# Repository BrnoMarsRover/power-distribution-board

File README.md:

# Power distribution board

Everything for the BrnoMarsRover power distribution board: the schematic and PCB, the
firmware that runs on it, and the ROS 2 driver that consumes it.

```
kicad/      schematic and PCB
pdf/        exported schematics
firmware/   Raspberry Pi Pico 2 sketch (Arduino, arduino-pico core)
ros2/       ROS 2 driver package (ament_python, Humble)
```

The firmware and the driver live together **because they share a versioned wire
protocol**. Every field name and status bit below is written twice - once in
`firmware/PowerBoard/Functions.cpp` and once in `ros2/powerboard/powerboard/powerboard_node.py`.
Splitting them across repositories would let the two halves be changed, reviewed and
deployed independently, and the failure mode is not a build error - it is silently
misparsed telemetry. Change the protocol in one commit, and bump `jsonSchemaVersion`
(firmware `Config.cpp`) together with `SUPPORTED_SCHEMA` (node) when you do.

## Hardware

Five INA238 current/voltage monitors on I2C, one per branch, each with a high-side
switch:

| Designator | I2C  | Shunt  | Rail             | Limit   |
|-----------|------|--------|------------------|---------|
| U2        | 0x40 | 3 mOhm | battery feed, and the master gate for the rest | 15 A |
| U3        | 0x41 | 5 mOhm | 24 V             | 2.5 A   |
| U4        | 0x42 | 5 mOhm | 15 V             | 4 A     |
| U5        | 0x43 | 5 mOhm | 12 V             | 5 A     |
| U6        | 0x44 | 5 mOhm | 5 V              | 12 A    |

Limits come from the 60 W rating of each DC-DC converter.

**Over-current protection ships disabled** (`ocpEnabled = false`). Some high-side
drivers were tripped by inrush and are bridged, so the board cannot actually switch
those branches off. Limits are still evaluated and reported, so an overload is visible
in telemetry even though nothing acts on it. `OCP ON` enables tripping if the hardware
is ever repaired.

Two things the board cannot measure, by construction:

- **Charging current.** The charger is wired on the battery side of U2's shunt, so
  charge current never crosses it. The driver infers charging from rising open-circuit
  voltage instead.
- **Currents above ~8 A on the INA CURRENT register**, which saturates there. The
  shunt-derived value is used for protection and for the `i` field because it has the
  range; `ir` is kept alongside it only for cross-checking.

## Serial protocol (schema v1)

USB CDC-ACM, one JSON object per line, telemetry at 2 Hz. Anything not starting with
`{` is human-readable diagnostics (`STATUS`, `RAW`) and is ignored by machine readers.

`"t"` gives the line type: `tel`, `evt`, `ack`, `err`, `info`.

### `tel` - periodic telemetry

```json
{"t":"tel","v":1,"seq":123,"up":61500,"ocp":0,"mst":1,"b":[ ... ]}
```

| Key   | Meaning                                        |
|-------|------------------------------------------------|
| `v`   | schema version                                  |
| `seq` | frame counter; gaps mean frames were lost       |
| `up`  | milliseconds since board boot                   |
| `ocp` | 1 if over-current protection is enabled         |
| `mst` | 1 if the U2 master branch is on                 |
| `b`   | one object per branch                           |

Each branch object:

| Key   | Unit | Meaning                                                   |
|-------|------|-----------------------------------------------------------|
| `n`   |      | designator, `U2`..`U6`                                    |
| `a`   |      | I2C address                                               |
| `s`   |      | status bits, see below                                    |
| `lim` | mA   | configured current limit                                  |
| `vb`  | V    | bus voltage                                               |
| `vs`  | mV   | shunt voltage                                             |
| `i`   | mA   | current derived from the shunt - **this is the real one** |
| `ir`  | mA   | INA CURRENT register, saturates at ~8 A, cross-check only |
| `tc`  | degC | INA die temperature                                       |
| `tr`  |      | cumulative trip count                                     |

Status bits in `s`:

| Bit  | Name        |
|------|-------------|
| 0x01 | online      |
| 0x02 | enabled     |
| 0x04 | tripped     |
| 0x08 | manual off  |
| 0x10 | powered     |
| 0x20 | over limit  |

### `evt` - pushed immediately, not on the telemetry tick

```json
{"t":"evt","up":61500,"ev":"over_limit","n":"U5","i":5200.0,"lim":5000,"ocp":0}
```

`ev` is one of `over_limit`, `over_limit_clear`, `ocp_trip`, `ocp_recover`. These are
pushed as they happen because with OCP disabled an over-limit event is the only
actionable signal the board can give.

### `ack` / `err` / `info`

```json
{"t":"ack","cmd":"JSON","msg":"json output"}
{"t":"err","cmd":"OFF U9","msg":"unknown branch"}
{"t":"info","fw":"...","v":1,"rails":5,"ocp":0}
```

### Commands (host to board, one per line)

| Command        | Effect                                          |
|----------------|-------------------------------------------------|
| `ON <U>`       | switch a branch on                              |
| `OFF <U>`      | switch a branch off                             |
| `OCP [ON|OFF]` | query or set over-current protection            |
| `RAW`          | dump every INA238 register, human readable      |
| `STATUS`       | human readable summary                          |
| `JSON`         | machine-readable output (the default)           |
| `HUMAN`        | switch to the plain-text table                  |
| `ONCE`         | emit a single telemetry frame                   |

## Firmware

Arduino sketch in `firmware/PowerBoard`, target Raspberry Pi Pico 2 (`rpipico2`),
arduino-pico core 5.5.1. Open `PowerBoard.ino` and flash it.

## ROS 2 driver

`ros2/powerboard`, ament_python, tested on Humble. Depends only on `rclpy`,
`std_msgs`, `sensor_msgs`, `diagnostic_msgs` and `python3-serial` - no custom
interfaces.

```bash
ros2 launch powerboard powerboard.launch.py
```

| Topic                | Type                       |
|----------------------|----------------------------|
| `~/battery`          | `sensor_msgs/BatteryState` |
| `~/rails/voltages`   | `std_msgs/Float32MultiArray` |
| `~/rails/currents`   | `std_msgs/Float32MultiArray` |
| `~/rails/powers`     | `std_msgs/Float32MultiArray` |
| `~/events`           | `std_msgs/String`          |
| `~/command`          | `std_msgs/String` (subscription, forwards any board command) |
| `/diagnostics`       | `diagnostic_msgs/DiagnosticArray` |

The rail arrays carry names in `layout.dim[i].label`, index-aligned with `data[i]`.

State of charge is estimated from a LiPo open-circuit-voltage curve, load-compensated
and smoothed, and published in `BatteryState.percentage`. It is a rough guide, not a
fuel gauge: between about 3.8 and 3.9 V/cell the curve is nearly flat, and below
3.7 V/cell it falls away sharply. Defaults assume Freya's **10S, 14.5 Ah** pack; see
`cell_count`, `design_capacity_ah` and `pack_resistance_ohm`.

**Only one process may hold the serial port.** Two readers steal bytes from each other,
which looks exactly like a flaky board - sequence gaps and a halved frame rate.

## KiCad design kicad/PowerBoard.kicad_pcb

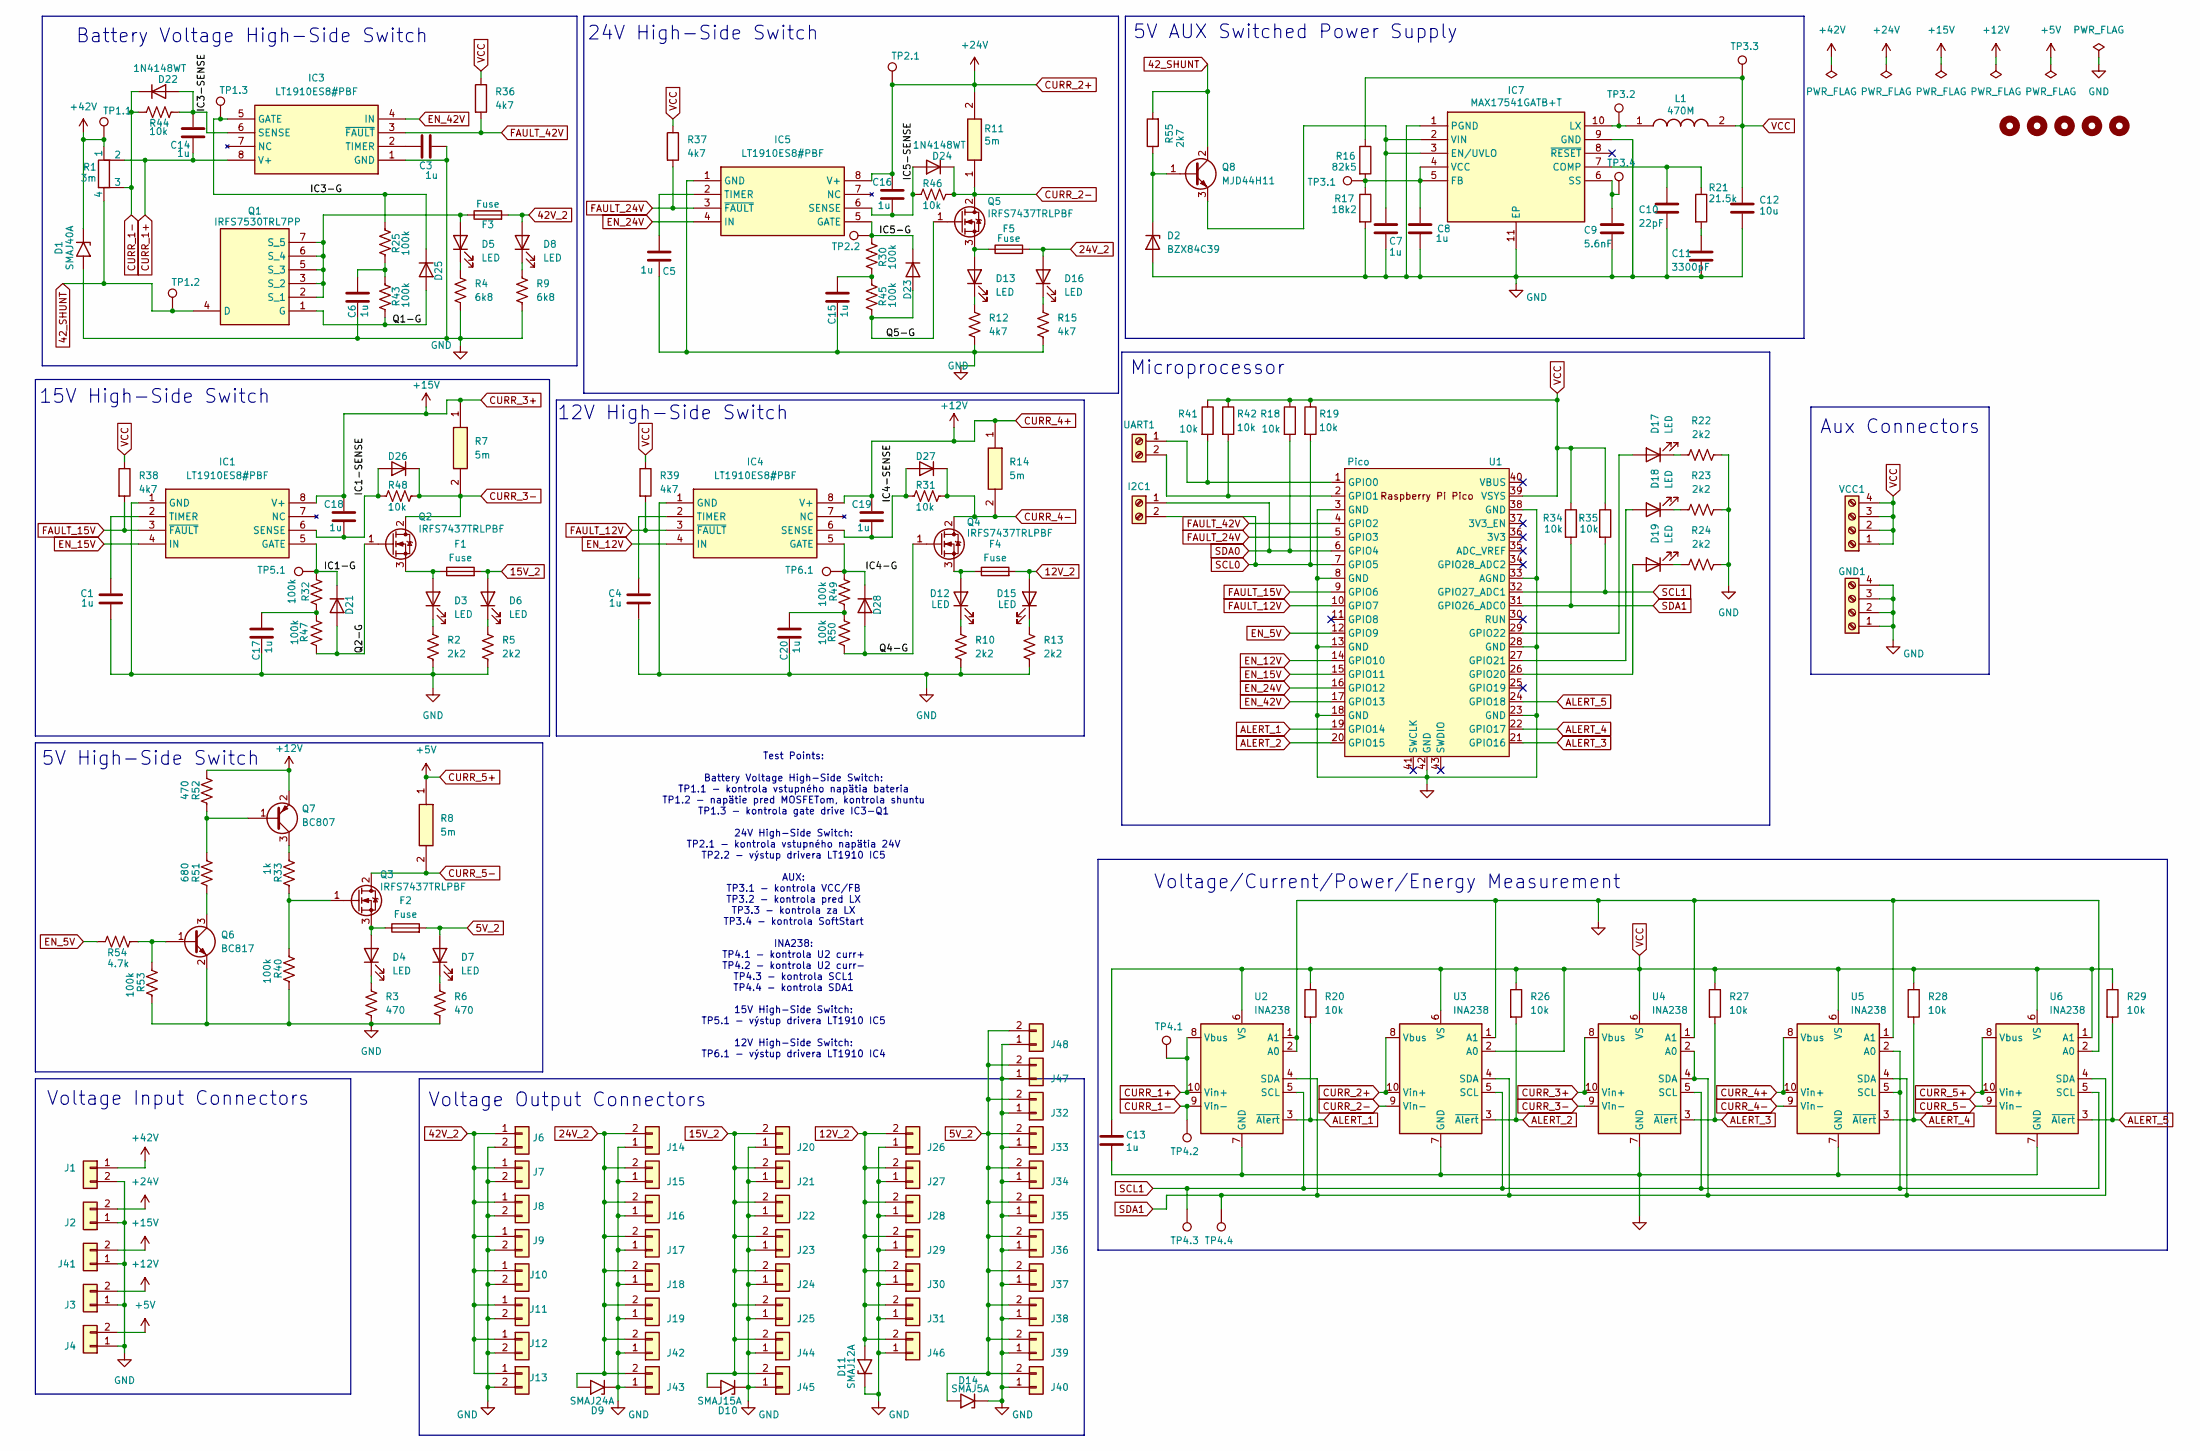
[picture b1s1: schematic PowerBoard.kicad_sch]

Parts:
C1, C3, C4, C5, C6, C7, C8, C14, C15, C16, C17, C18, C19, C20: 1u; C_0603_1608Metric
C9: 5.6nF; C_0603_1608Metric
C10: 22pF; C_0603_1608Metric
C11: 3300pF; C_0603_1608Metric
C12: 10u; C_0603_1608Metric
C13: 1u; C_1206_3216Metric
D1: SMAJ40A; D_SMA
D2: BZX84C39; SOT-23
D3, D4, D5, D6, D7, D8, D12, D13, D15, D16, D17, D18, D19: LED; D_1206_3216Metric
D9: SMAJ24A; D_SMA
D10: SMAJ15A; D_SMA
D11: SMAJ12A; D_SMA
D14: SMAJ5A; D_SMA
D21, D22, D23, D24, D25, D26, D27, D28: 1N4148WT; D_SOD-523
F1, F2, F3, F4, F5: Fuse; Fuse_Blade_ATO_directSolder
GND1: Screw_Terminal_01x04; TerminalBlock_Xinya_XY308-2.54-4P_1x04_P2.54mm_Horizontal
H1, H2, H3, H4, H5: MountingHole; MountingHole_3.2mm_M3
I2C1: Screw_Terminal_01x02; TerminalBlock_Xinya_XY308-2.54-2P_1x02_P2.54mm_Horizontal
IC1, IC3, IC4, IC5: LT1910ES8#PBF; SOIC127P599X175-8N; Mouser Part Number 584-LT1910ES8#PBF
IC7: MAX17541GATB+T; SON50P200X300X80-11N; Mouser Part Number 700-MAX17541GATB+T
J1, J6, J7, J8, J9, J10, J11, J12, J13: XT90
J2, J14, J15, J16, J17, J18, J19, J42, J43: DEAN_T; DEANS-T
J3, J20, J21, J22, J23, J24, J25, J26, J27, J28, J29, J30, J31, J41, J44, J45, J46: XT60; AMASS_XT60-F_1x02_P7.20mm_Vertical
J4, J32, J33, J34, J35, J36, J37, J38, J39, J40, J47, J48: XT30; AMASS_XT30U-F_1x02_P5.0mm_Vertical
L1: 470M; SRR5828A2R6Y; Mouser Part Number 6521-SRR5828A-470M
Q1: IRFS7530TRL7PP; Mouser Part Number 942-IRFS7530TRL7PP
Q2, Q3, Q4, Q5: IRFS7437TRLPBF; TO-263-2
Q6: BC817; SOT-23
Q7: BC807; SOT-23
Q8: MJD44H11; TO-252-2
R1: 3m; R_Shunt_Isabellenhuette_BVR4026
R2, R10: 2k2; R_0603_1608Metric
R3, R52: 470; R_0603_1608Metric
R4: 6k8; C_0603_1608Metric
R5, R13, R22, R23, R24: 2k2; R_1206_3216Metric
R6: 470; R_1206_3216Metric
R7, R8, R11, R14: 5m; RESC3216X89N; Mouser Part Number 71-WSL12061L000FEA
R9: 6k8; R_1206_3216Metric
R12: 4k7; R_0603_1608Metric
R15, R36, R37, R38, R39: 4k7; R_1206_3216Metric
R16: 82k5; R_0603_1608Metric
R17: 18k2; R_0603_1608Metric
R18, R19, R20, R26, R27, R28, R29, R34, R35, R41, R42: 10k; R_1206_3216Metric
R21: 21.5k; R_0603_1608Metric
R25, R30, R32, R40, R43, R45, R47, R49, R50, R53: 100k; R_0603_1608Metric
R31, R44, R46, R48: 10k; R_0603_1608Metric
R33: 1k; R_0603_1608Metric
R51: 680; R_0603_1608Metric
R54: 4.7k; R_0603_1608Metric
R55: 2k7; R_1206_3216Metric
TP1.1, TP1.2, TP1.3, TP2.1, TP2.2, TP3.1, TP3.2, TP3.3, TP3.4, TP4.1, TP4.2, TP4.3, TP4.4, TP5.1, TP6.1: TestPoint; TestPoint_Pad_1.0x1.0mm
U1: Pico; RPi_Pico_SMD_TH
U2, U3, U4, U5, U6: INA238; VSSOP-10_3x3mm_P0.5mm
UART1: Screw_Terminal_01x02; TerminalBlock_Xinya_XY308-2.54-2P_1x02_P2.54mm_Horizontal
VCC1: Screw_Terminal_01x04; TerminalBlock_Xinya_XY308-2.54-4P_1x04_P2.54mm_Horizontal

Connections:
5V_2: D7.2 (A), D14.2 (A2), F2.2, J32.2, J33.2, J34.2, J35.2, J36.2, J37.2, J38.2, J39.2, J40.2, J47.2, J48.2
12V_2: D11.2 (A2), D15.2 (A), F4.2, J26.2, J27.2, J28.2, J29.2, J30.2, J31.2, J46.2
15V_2: D6.2 (A), D10.2 (A2), F1.2, J20.2, J21.2, J22.2, J23.2, J24.2, J25.2, J44.2, J45.2
24V_2: D9.2 (A2), D16.2 (A), F5.2, J14.2, J15.2, J16.2, J17.2, J18.2, J19.2, J42.2, J43.2
42V_2: D8.2 (A), F3.2, J6.1, J7.1, J8.1, J9.1, J10.1, J11.1, J12.1, J13.1
42_SHUNT: Q1.4 (D), Q8.2 (C), R1.4, R55.2, TP1.2.1
+42V: D1.1 (A1), J1.1, R1.1, TP1.1.1
/IC1-G: D21.1 (K), IC1.5 (GATE), R32.2, TP5.1.1
/IC1-SENSE: C18.2, D26.2 (A), IC1.6 (SENSE), R48.1
/IC3-G: D25.1 (K), IC3.5 (GATE), R25.2, TP1.3.1
/IC3-SENSE: C14.1, D22.2 (A), IC3.6 (SENSE), R44.2
/IC4-G: D28.1 (K), IC4.5 (GATE), R49.2, TP6.1.1
/IC4-SENSE: C19.2, D27.2 (A), IC4.6 (SENSE), R31.1
/IC5-G: D23.1 (K), IC5.5 (GATE), R30.2, TP2.2.1
/IC5-SENSE: C16.2, D24.2 (A), IC5.6 (SENSE), R46.1
/Q1-G: D25.2 (A), Q1.1 (G), R43.2
/Q2-G: D21.2 (A), Q2.1 (G), R47.2
/Q4-G: D28.2 (A), Q4.1 (G), R50.2
/Q5-G: D23.2 (A), Q5.1 (G), R45.2
ALERT_1: R20.2, U1.19 (GPIO14), U2.3 (~Alert)
ALERT_2: R26.2, U1.20 (GPIO15), U3.3 (~Alert)
ALERT_3: R27.2, U1.21 (GPIO16), U4.3 (~Alert)
ALERT_4: R28.2, U1.22 (GPIO17), U5.3 (~Alert)
ALERT_5: R29.2, U1.24 (GPIO18), U6.3 (~Alert)
CURR_1+: C14.2, IC3.8 (V+), R1.2, TP4.1.1, U2.8 (Vbus), U2.10 (Vin+)
CURR_1-: D22.1 (K), R1.3, R44.1, TP4.2.1, U2.9 (Vin-)
CURR_2+: C16.1, IC5.8 (V+), J2.2, R11.2, TP2.1.1, U3.8 (Vbus), U3.10 (Vin+)
CURR_2-: D24.1 (K), Q5.2 (D), R11.1, R46.2, U3.9 (Vin-)
CURR_3+: C18.1, IC1.8 (V+), J41.2, R7.1, U4.8 (Vbus), U4.10 (Vin+)
CURR_3-: D26.1 (K), Q2.2 (D), R7.2, R48.2, U4.9 (Vin-)
CURR_4+: C19.1, IC4.8 (V+), J3.2, Q7.2 (E), R14.1, R52.2, U5.8 (Vbus), U5.10 (Vin+)
CURR_4-: D27.1 (K), Q4.2 (D), R14.2, R31.2, U5.9 (Vin-)
CURR_5+: J4.2, R8.1, U6.8 (Vbus), U6.10 (Vin+)
CURR_5-: Q3.2 (D), R8.2, U6.9 (Vin-)
EN_5V: R54.2, U1.12 (GPIO9)
EN_12V: IC4.4 (IN), U1.14 (GPIO10)
EN_15V: IC1.4 (IN), U1.15 (GPIO11)
EN_24V: IC5.4 (IN), U1.16 (GPIO12)
EN_42V: IC3.4 (IN), U1.17 (GPIO13)
FAULT_12V: IC4.3 (~FAULT), R39.2, U1.10 (GPIO7)
FAULT_15V: IC1.3 (~FAULT), R38.2, U1.9 (GPIO6)
FAULT_24V: IC5.3 (~FAULT), R37.2, U1.5 (GPIO3)
FAULT_42V: IC3.3 (~FAULT), R36.2, U1.4 (GPIO2)
GND: C1.2, C3.2, C4.2, C5.2, C6.1, C7.2, C8.2, C9.2, C10.2, C11.2, C12.2, C13.2, C15.1, C17.1, C20.1, D1.2 (A2), D2.1 (A), D9.1 (A1), D10.1 (A1), D11.1 (A1), D14.1 (A1), GND1.1, GND1.2, GND1.3, GND1.4, IC1.1 (GND), IC3.1 (GND), IC4.1 (GND), IC5.1 (GND), IC7.1 (PGND), IC7.9 (GND), IC7.11 (EP), J1.2, J2.1, J3.1, J4.1, J6.2, J7.2, J8.2, J9.2, J10.2, J11.2, J12.2, J13.2, J14.1, J15.1, J16.1, J17.1, J18.1, J19.1, J20.1, J21.1, J22.1, J23.1, J24.1, J25.1, J26.1, J27.1, J28.1, J29.1, J30.1, J31.1, J32.1, J33.1, J34.1, J35.1, J36.1, J37.1, J38.1, J39.1, J40.1, J41.1, J42.1, J43.1, J44.1, J45.1, J46.1, J47.1, J48.1, Q6.2 (E), R2.2, R3.2, R4.2, R5.2, R6.2, R9.2, R10.2, R12.2, R13.2, R15.2, R17.2, R22.2, R23.2, R24.2, R40.1, R53.1, U1.3 (GND), U1.8 (GND), U1.13 (GND), U1.18 (GND), U1.23 (GND), U1.28 (GND), U1.33 (AGND), U1.38 (GND), U1.42 (GND), U2.1 (A1), U2.2 (A0), U2.7 (GND), U3.1 (A1), U3.7 (GND), U4.1 (A1), U4.7 (GND), U5.1 (A1), U5.7 (GND), U6.2 (A0), U6.7 (GND)
unnamed: C6.2, R25.1, R43.1
unnamed: C11.1, R21.2
unnamed: C15.2, R30.1, R45.1
unnamed: C17.2, R32.1, R47.1
unnamed: C20.2, R49.1, R50.1
unnamed: D2.3 (K), Q8.1 (B), R55.1
unnamed: D3.2 (A), F1.1, Q2.3 (S)
unnamed: D3.1 (K), R2.1
unnamed: D4.2 (A), F2.1, Q3.3 (S)
unnamed: D4.1 (K), R3.1
unnamed: D5.2 (A), F3.1, Q1.2 (S_1), Q1.3 (S_2), Q1.5 (S_3), Q1.6 (S_4), Q1.7 (S_5)
unnamed: D5.1 (K), R4.1
unnamed: D6.1 (K), R5.1
unnamed: D7.1 (K), R6.1
unnamed: D8.1 (K), R9.1
unnamed: D12.2 (A), F4.1, Q4.3 (S)
unnamed: D12.1 (K), R10.1
unnamed: D13.2 (A), F5.1, Q5.3 (S)
unnamed: D13.1 (K), R12.1
unnamed: D15.1 (K), R13.1
unnamed: D16.1 (K), R15.1
unnamed: D17.2 (A), U1.29 (GPIO22)
unnamed: D17.1 (K), R22.1
unnamed: D18.2 (A), U1.27 (GPIO21)
unnamed: D18.1 (K), R23.1
unnamed: D19.2 (A), U1.26 (GPIO20)
unnamed: D19.1 (K), R24.1
unnamed: C1.1, IC1.2 (TIMER)
unnamed: C3.1, IC3.2 (TIMER)
unnamed: C4.1, IC4.2 (TIMER)
unnamed: C5.1, IC5.2 (TIMER)
unnamed: C10.1, IC7.7 (COMP), R21.1
unnamed: C7.1, IC7.2 (VIN), IC7.3 (EN/UVLO), Q8.3 (E)
unnamed: C8.1, IC7.4 (VCC), IC7.5 (FB), R16.2, R17.1, TP3.1.1
unnamed: IC7.10 (LX), L1.1, TP3.2.1
unnamed: C9.1, IC7.6 (SS), TP3.4.1
unnamed: Q3.1 (G), R33.1, R40.2
unnamed: Q6.1 (B), R53.2, R54.1
unnamed: Q6.3 (C), R51.1
unnamed: Q7.1 (B), R51.2, R52.1
unnamed: Q7.3 (C), R33.2
unnamed: R41.2, U1.1 (GPIO0), UART1.1
unnamed: R42.2, U1.2 (GPIO1), UART1.2
SCL0: I2C1.2, R19.2, U1.7 (GPIO5)
SCL1: R35.2, TP4.3.1, U1.32 (GPIO27_ADC1), U2.5 (SCL), U3.5 (SCL), U4.5 (SCL), U5.2 (A0), U5.5 (SCL), U6.5 (SCL)
SDA0: I2C1.1, R18.2, U1.6 (GPIO4)
SDA1: R34.2, TP4.4.1, U1.31 (GPIO26_ADC0), U2.4 (SDA), U3.4 (SDA), U4.2 (A0), U4.4 (SDA), U5.4 (SDA), U6.4 (SDA)
VCC: C12.1, C13.1, L1.2, R16.1, R18.1, R19.1, R20.1, R26.1, R27.1, R28.1, R29.1, R34.1, R35.1, R36.1, R37.1, R38.1, R39.1, R41.1, R42.1, TP3.3.1, U1.39 (VSYS), U2.6 (VS), U3.2 (A0), U3.6 (VS), U4.6 (VS), U5.6 (VS), U6.1 (A1), U6.6 (VS), VCC1.1, VCC1.2, VCC1.3, VCC1.4

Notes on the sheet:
12V High-Side Switch
24V High-Side Switch
Voltage/Current/Power/Energy Measurement
Aux Connectors
15V High-Side Switch
Microprocessor
Battery Voltage High-Side Switch
5V High-Side Switch
Test Points: Battery Voltage High-Side Switch: TP1.1 - kontrola vstupného napätia bateria TP1.2 - napätie pred MOSFETom, kontrola shuntu TP1.3 - kontrola gate drive IC3-Q1 24V High-Side Switch: TP2.1 - kontrola vstupného napätia 24V TP2.2 - výstup drivera LT1910 IC5 AUX: TP3.1 - kontrola VCC/FB TP3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
Voltage Output Connectors
Voltage Input Connectors
5V AUX Switched Power Supply

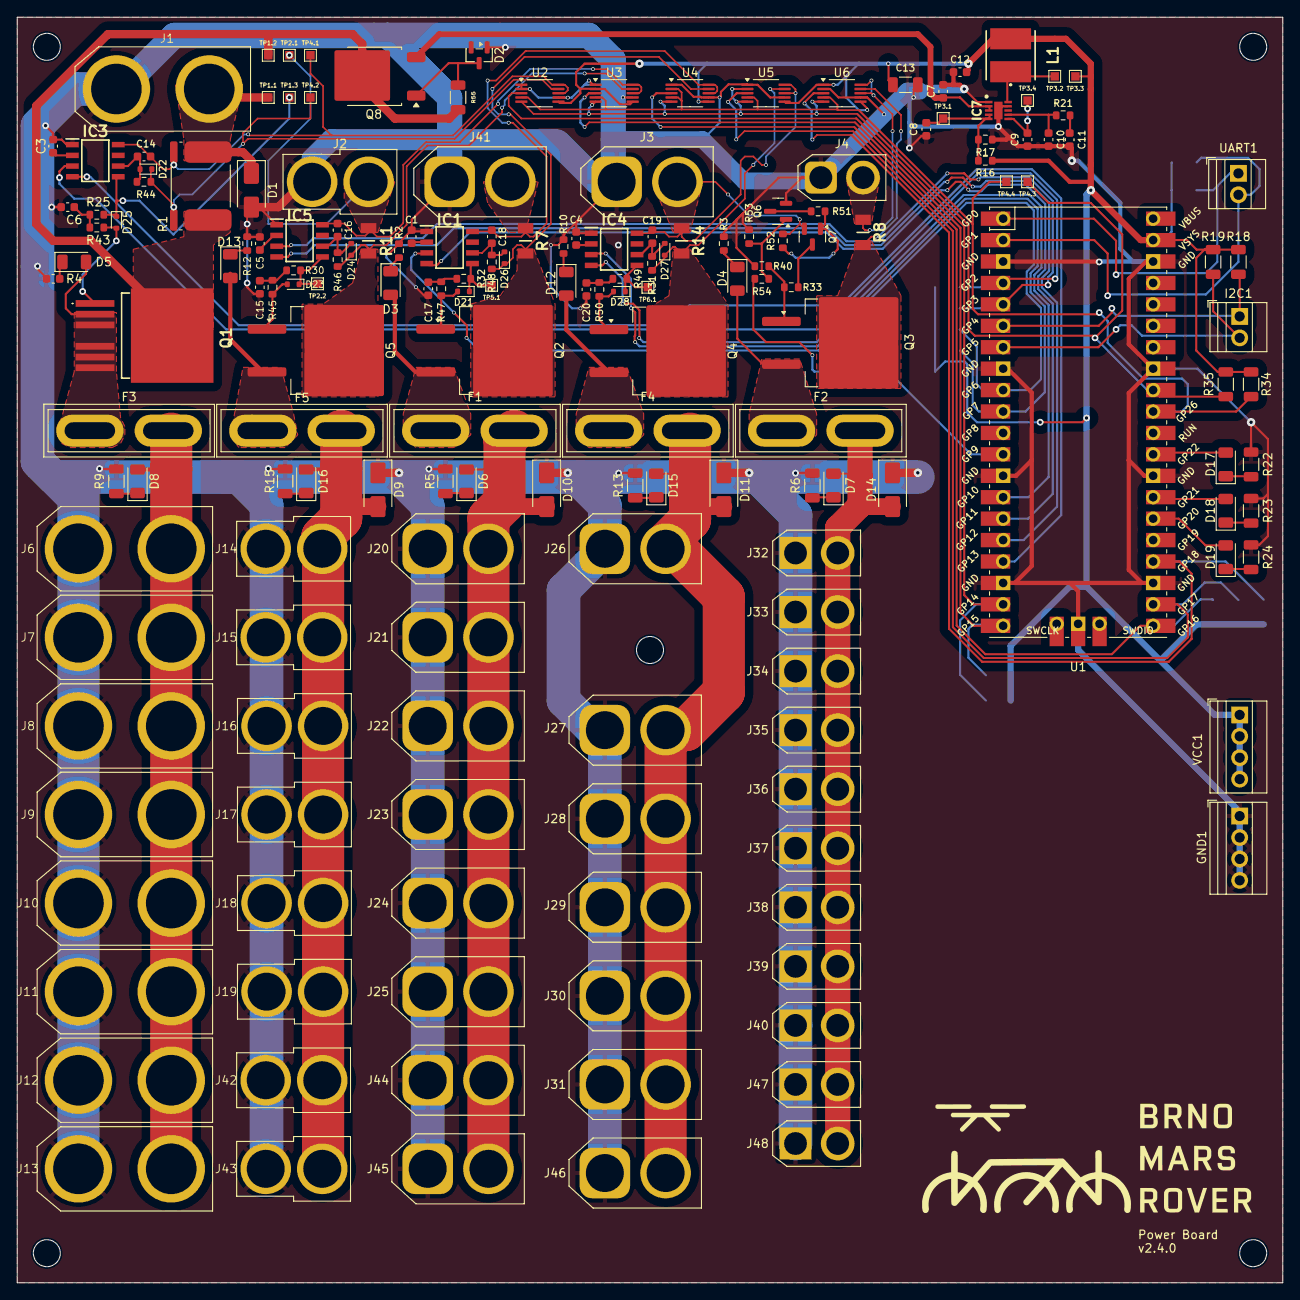
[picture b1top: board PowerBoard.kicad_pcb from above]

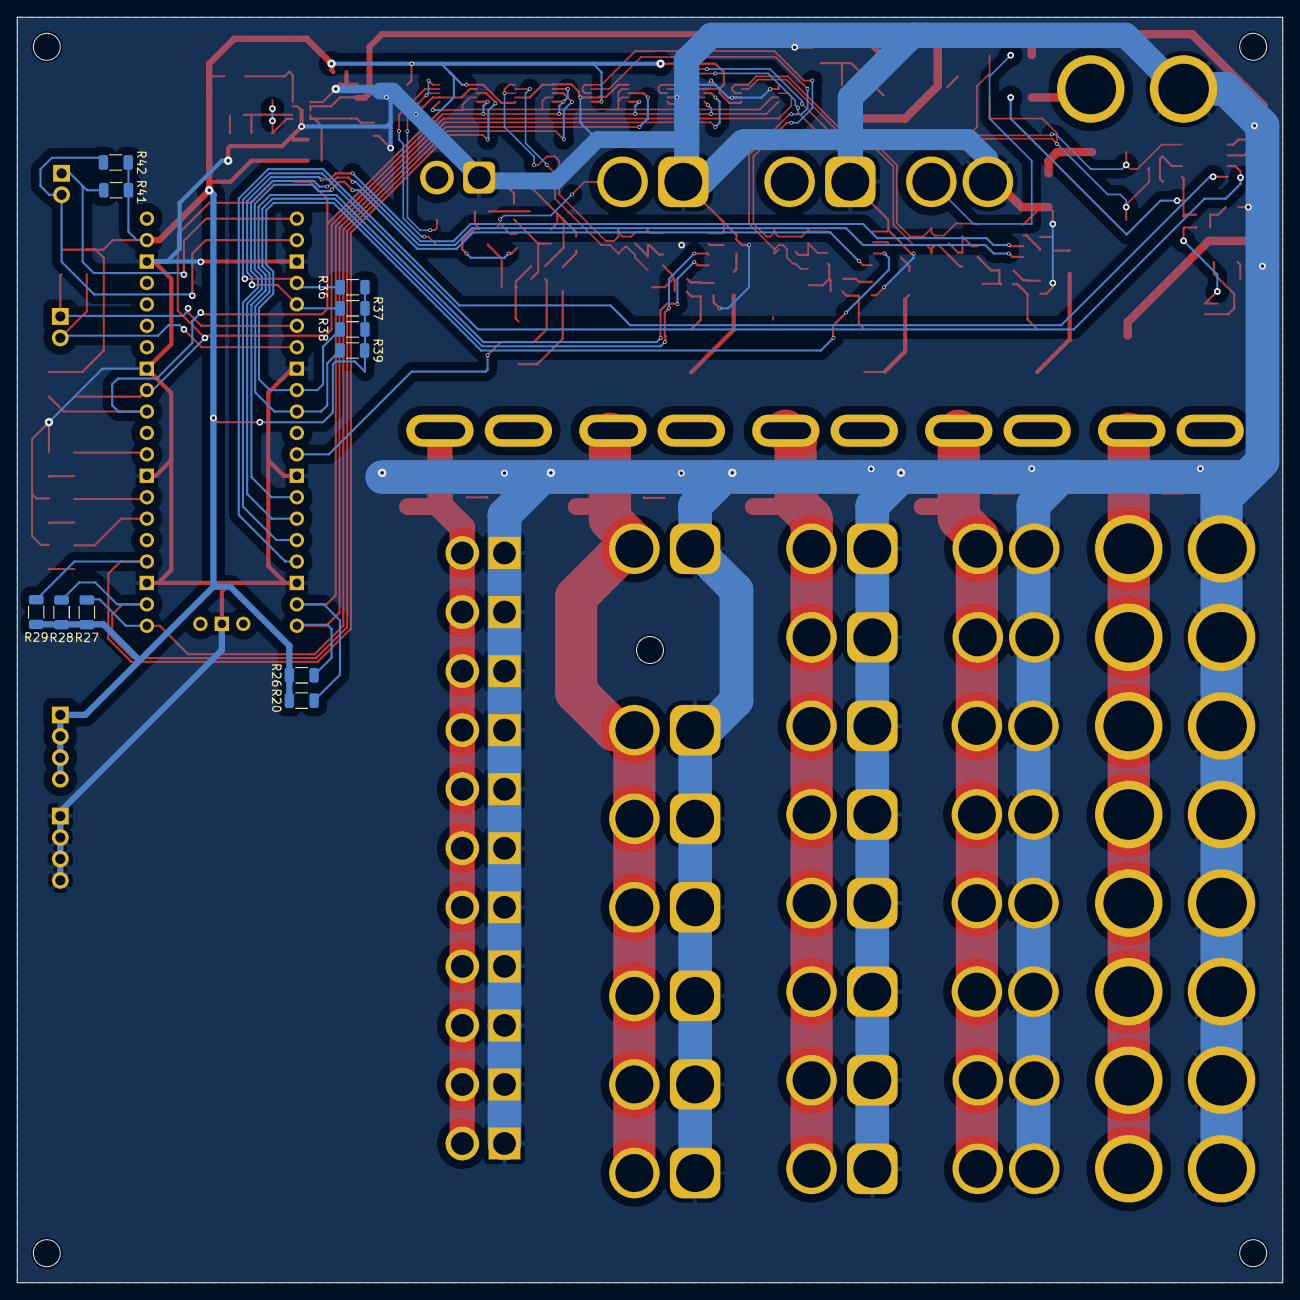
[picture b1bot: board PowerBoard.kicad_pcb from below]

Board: 2 copper layers, 150.0 x 150.0 mm, 197 parts (11 on the bottom side), 92 nets.

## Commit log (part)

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2024-10-10 v2.0.2
2024-10-11 added status leds
2024-11-01 changed i2c connection
2024-11-01 added spi and i2c terminals
2024-11-01 sync
2024-12-02 Remove unused switch on the battery rail
2024-12-03 Add LTC7004 driver
2024-12-03 iterate the layoutL
2024-12-05 fix the layout
2024-12-06 change input mosfet for a supported one
2024-12-13 Finish the design
2024-12-16 v2.2.0
2024-12-21 add base resistors for the power mosfets
2024-12-21 change shunt value
2024-12-21 Adjust resistor and transil values
2024-12-21 update bom
2024-12-28 remove solder mask from high current traces and optimize vias for cheaper manufacturing process
2025-01-23 safety features added, uart connector added
2025-01-28 Add first firmware version
2025-06-16 Add dV/dt for inrush current limitation on the main power line
2025-06-19 finish inrush current limiting
2025-06-20 finish v2.4.0
2025-06-20 rework the 5V switching
2025-06-24 adjust component values
2026-03-15 Add files via upload
    - Použitie normovaných hodnôt súčiastok v dizajne
    Opravený typ diód a hodnota D9,D10,D11,D14.
    Opravená orientácia diód D9, D10, D11, D14.
    - Zmeny hodnôt komponentov
    Opravene hodnoty komponentov:
    5,5nF -> 5,6nF
2026-03-15 Generate gerber production files
